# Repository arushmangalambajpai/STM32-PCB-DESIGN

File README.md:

# STM32 PCB Project

## Overview
This repository contains the design files and documentation for a custom PCB based on the STM32 microcontroller, created using KiCAD.

## Features
- **Microcontroller:** STM32 series (e.g., STM32F4xxx, STM32L0xxx)
- **Peripherals:** Includes GPIO, ADC, DAC, PWM, timers, and communication interfaces such as USB, UART, SPI, and I2C.
- **Connectivity:** Supports various communication protocols for IoT applications.
- **Power:** Operates within a specific voltage range (e.g., 3.3V or 5V) with low power consumption capabilities.
- **Programming:** Easily programmable via SWD interface or USB bootloader.
- **Dimensions:** Compact size suitable for embedded applications.

## Files Included
- **Schematic:** https://github.com/arushmangalambajpai/STM32-PCB-DESIGN/blob/main/STM32%40CRISS.kicad_sch
- **PCB Layout:** https://github.com/arushmangalambajpai/STM32-PCB-DESIGN/blob/main/STM32%40CRISS.kicad_pcb
- **Bill of Materials (BOM):** https://github.com/arushmangalambajpai/STM32-PCB-DESIGN/blob/main/BOM%40STM32_FINAL.xlsx

## Prerequisites
- **KiCAD:** Version X.X or higher. Download and install KiCAD from [KiCAD's official website](https://www.kicad.org/download/).

---

This README file provides a concise overview of your STM32 PCB project, detailing its features, the tools used, and where to find the necessary design files.

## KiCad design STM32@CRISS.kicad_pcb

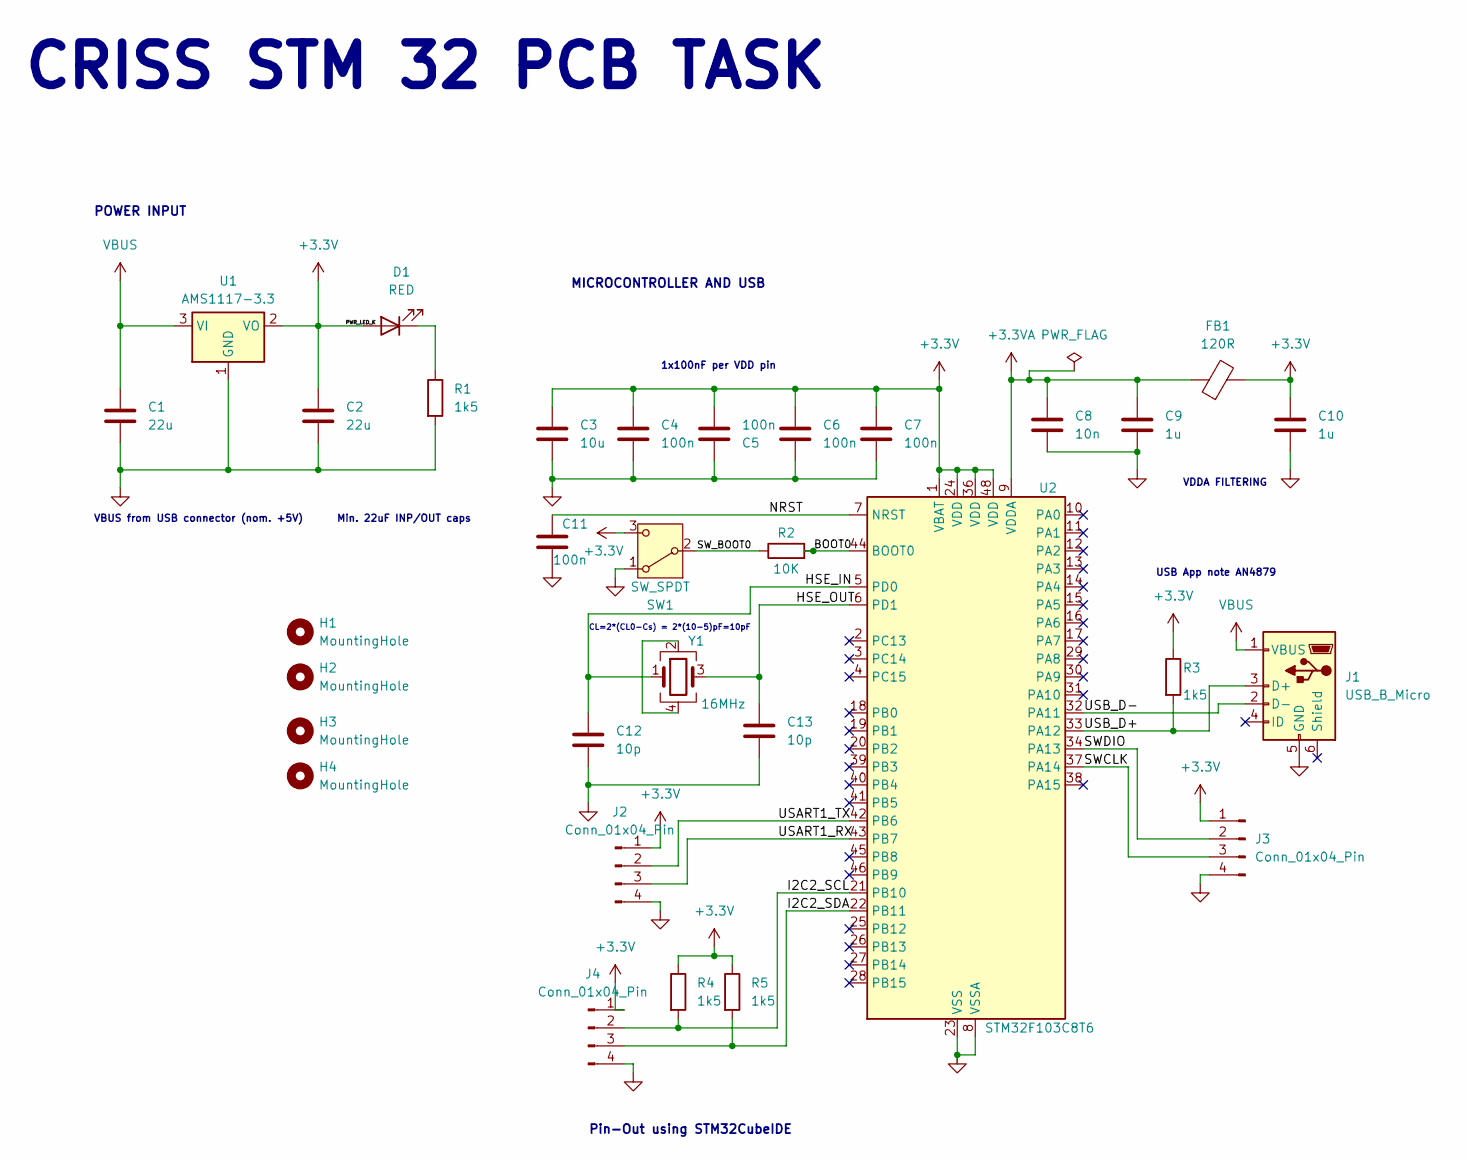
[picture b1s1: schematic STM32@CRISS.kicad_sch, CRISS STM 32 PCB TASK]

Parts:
C1, C2: 22u; C_0805_2012Metric
C3: 10u; C_0603_1608Metric
C4, C5, C6, C7, C11: 100n; C_0402_1005Metric
C8: 10n; C_0402_1005Metric
C9, C10: 1u; C_0402_1005Metric
C12, C13: 10p; C_0402_1005Metric
D1: RED; LED_0603_1608Metric
FB1: 120R; L_0603_1608Metric
H1, H2, H3, H4: MountingHole; MountingHole_2.1mm
J1: USB_B_Micro; USB_Micro-B_Wuerth_629105150521
J2, J3, J4: Conn_01x04_Pin; PinHeader_1x04_P2.54mm_Vertical
R1, R3, R4, R5: 1k5; R_0402_1005Metric
R2: 10K; R_0402_1005Metric
SW1: SW_SPDT; SW_SPDT_PCM12
U1: AMS1117-3.3; SOT-223-3_TabPin2
U2: STM32F103C8T6; LQFP-48_7x7mm_P0.5mm
Y1: 16MHz; Crystal_SMD_3225-4Pin_3.2x2.5mm

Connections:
+3.3V: C2.1, C3.1, C4.1, C5.2, C6.1, C7.1, C10.1, D1.2 (A), FB1.2, J2.1, J3.1, J4.1, R3.1, R4.1, R5.1, SW1.3 (C), U1.2 (VO), U2.1 (VBAT), U2.24 (VDD), U2.36 (VDD), U2.48 (VDD)
+3.3VA: C8.1, C9.1, FB1.1, U2.9 (VDDA)
/BOOT0: R2.2, U2.44 (BOOT0)
/HSE_IN: C12.1, U2.5 (PD0), Y1.1
/HSE_OUT: C13.1, U2.6 (PD1), Y1.3
/I2C2_SCL: J4.2, R4.2, U2.21 (PB10)
/I2C2_SDA: J4.3, R5.2, U2.22 (PB11)
/NRST: C11.1, U2.7 (NRST)
/SWCLK: J3.3, U2.37 (PA14)
/SWDIO: J3.2, U2.34 (PA13)
/SW_BOOT0: R2.1, SW1.2 (B)
/USART1_RX: J2.3, U2.43 (PB7)
/USART1_TX: J2.2, U2.42 (PB6)
/USB_D+: J1.3 (D+), R3.2, U2.33 (PA12)
/USB_D-: J1.2 (D-), U2.32 (PA11)
GND: C1.2, C2.2, C3.2, C4.2, C5.1, C6.2, C7.2, C8.2, C9.2, C10.2, C11.2, C12.2, C13.2, J1.5 (GND), J2.4, J3.4, J4.4, R1.2, SW1.1 (A), U1.1 (GND), U2.8 (VSSA), U2.23 (VSS), U2.35 (VSS), U2.47 (VSS)
unnamed: D1.1 (K), R1.1
unnamed: Y1.2, Y1.4
VBUS: C1.1, J1.1 (VBUS), U1.3 (VI)

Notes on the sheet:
CRISS STM 32 PCB TASK
MICROCONTROLLER AND USB
1x100nF per VDD pin
VDDA FILTERING
Pin-Out using STM32CubeIDE
Min. 22uF INP/OUT caps
CL=2*(CL0-Cs) = 2*(10-5)pF=10pF
POWER INPUT
USB App note AN4879
VBUS from USB connector (nom. +5V)

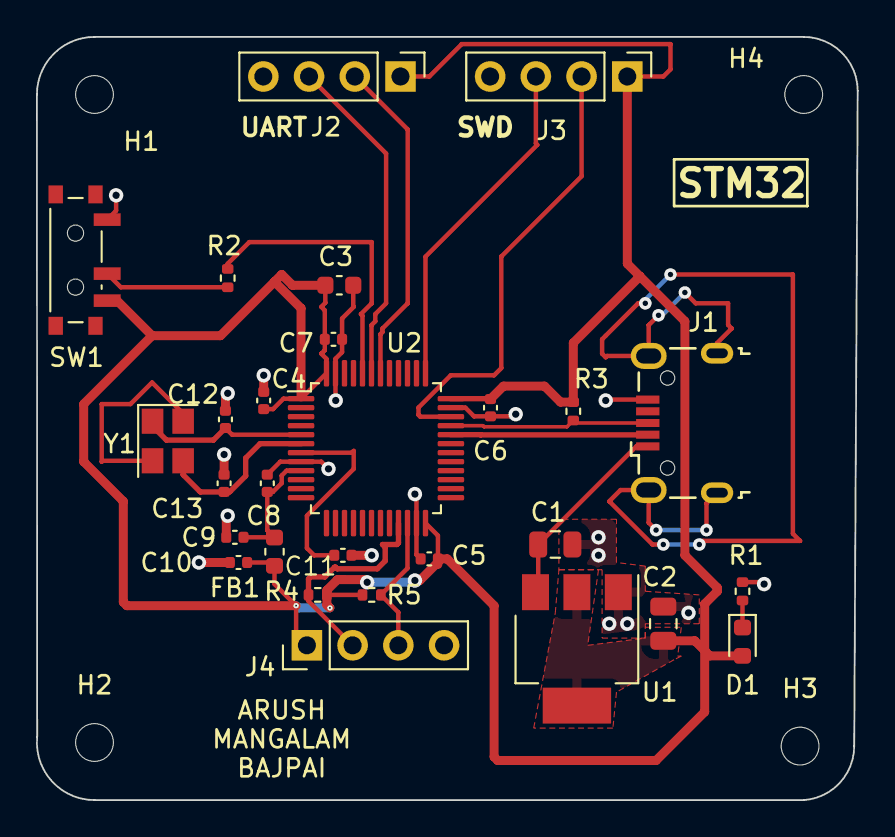
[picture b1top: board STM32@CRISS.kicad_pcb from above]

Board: 2 copper layers, 45.6 x 42.4 mm, 32 parts (0 on the bottom side), 19 nets.

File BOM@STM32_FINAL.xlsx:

Id | Designator | Footprint | Quantity | Designation
1 | R4,R1,R3,R5 | R_0402_1005Metric | 4 | 1k5
2 | C5,C4,C7,C11,C6 | C_0402_1005Metric | 5 | 100n
3 | U1 | SOT-223-3_TabPin2 | 1 | AMS1117-3.3
4 | J2,J4,J3 | PinHeader_1x04_P2.54mm_Vertical | 3 | Conn_01x04_Pin
5 | C10,C9 | C_0402_1005Metric | 2 | 1u
6 | C1,C2 | C_0805_2012Metric | 2 | 22u
7 | C13,C12 | C_0402_1005Metric | 2 | 10p
8 | SW1 | SW_SPDT_PCM12 | 1 | SW_SPDT
9 | Y1 | Crystal_SMD_3225-4Pin_3.2x2.5mm | 1 | 16MHz
10 | U2 | LQFP-48_7x7mm_P0.5mm | 1 | STM32F103C8T6
11 | H4,H3,H1,H2 | MountingHole_2.1mm | 4 | MountingHole
12 | D1 | LED_0603_1608Metric | 1 | RED
13 | FB1 | L_0603_1608Metric | 1 | 120R
14 | C8 | C_0402_1005Metric | 1 | 10n
15 | C3 | C_0603_1608Metric | 1 | 10u
16 | R2 | R_0402_1005Metric | 1 | 10K
17 | J1 | USB_Micro-B_Wuerth_629105150521 | 1 | USB_B_Micro

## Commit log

2024-06-24 add files
